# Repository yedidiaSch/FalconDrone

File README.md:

# FalconDrone - RTOS Based Flight Controller

## Project Overview
FalconDrone is an ongoing development of a quadcopter flight control system built from scratch using the **STM32F446RE (Nucleo)** platform. The project focuses on implementing high-performance real-time estimation and control algorithms within a **FreeRTOS** environment.

The current milestone focuses on a "Studio-Tethered" stabilization mode, ensuring the drone maintains its attitude (Roll/Pitch) while secured to a test bench.

## System Architecture
The firmware is designed with a modular, object-oriented approach in C++, emphasizing non-blocking operations and efficient resource management.

### Key Features
* **Real-Time Kernel:** Task management and scheduling via FreeRTOS.
* **Asynchronous I/O:** MPU6050 IMU data acquisition using **I2C DMA** to minimize CPU overhead.
* **Thread-Safe Logging:** Custom UART logging mechanism utilizing **DMA** and FreeRTOS Queues for non-blocking telemetry.
* **Attitude Estimation:** Implementation of raw sensor data processing (Accelerometer and Gyroscope) for Roll/Pitch calculation.

## Hardware Stack
* **MCU:** STM32F446RE (ARM Cortex-M4 @ 180MHz)
* **IMU:** MPU6050 (3-Axis Accelerometer & Gyroscope)
* **Frame:** F450 Quadcopter Frame
* **Motors:** A2212 1000KV Brushless Motors
* **ESCs:** 30A Brushless XXD
* **Power:** 3S Lipo 2200mAh 11.1V

## Software Stack
* **Language:** C++ / C
* **OS:** FreeRTOS
* **Framework:** STM32Cube HAL
* **Build System:** CMake
* **Development Env:** VS Code on Ubuntu

## Current Status: Attitude Estimation Phase
The system currently performs the following:
1.  Initializes hardware peripherals (I2C, UART, DMA, GPIO).
2.  Starts the FreeRTOS scheduler.
3.  Continuously streams 14-byte IMU data packets via DMA.
4.  Processes raw data into Euler angles (Roll and Pitch).

### Forthcoming Milestones
* **Sensor Fusion:** Implementation of a Complementary Filter or Kalman Filter to reduce accelerometer noise and gyroscope drift.
* **PID Control:** Development of the attitude control loop for motor speed regulation.
* **PWM Generation:** Utilizing Timer peripherals to drive ESCs.

## Setup and Installation

### Prerequisites
* GNU Arm Embedded Toolchain
* CMake (minimum 3.10)
* STM32CubeMX (for peripheral configuration)
* OpenOCD / ST-Link Utilities

### Building
```bash
mkdir build
cd build
cmake ..
make

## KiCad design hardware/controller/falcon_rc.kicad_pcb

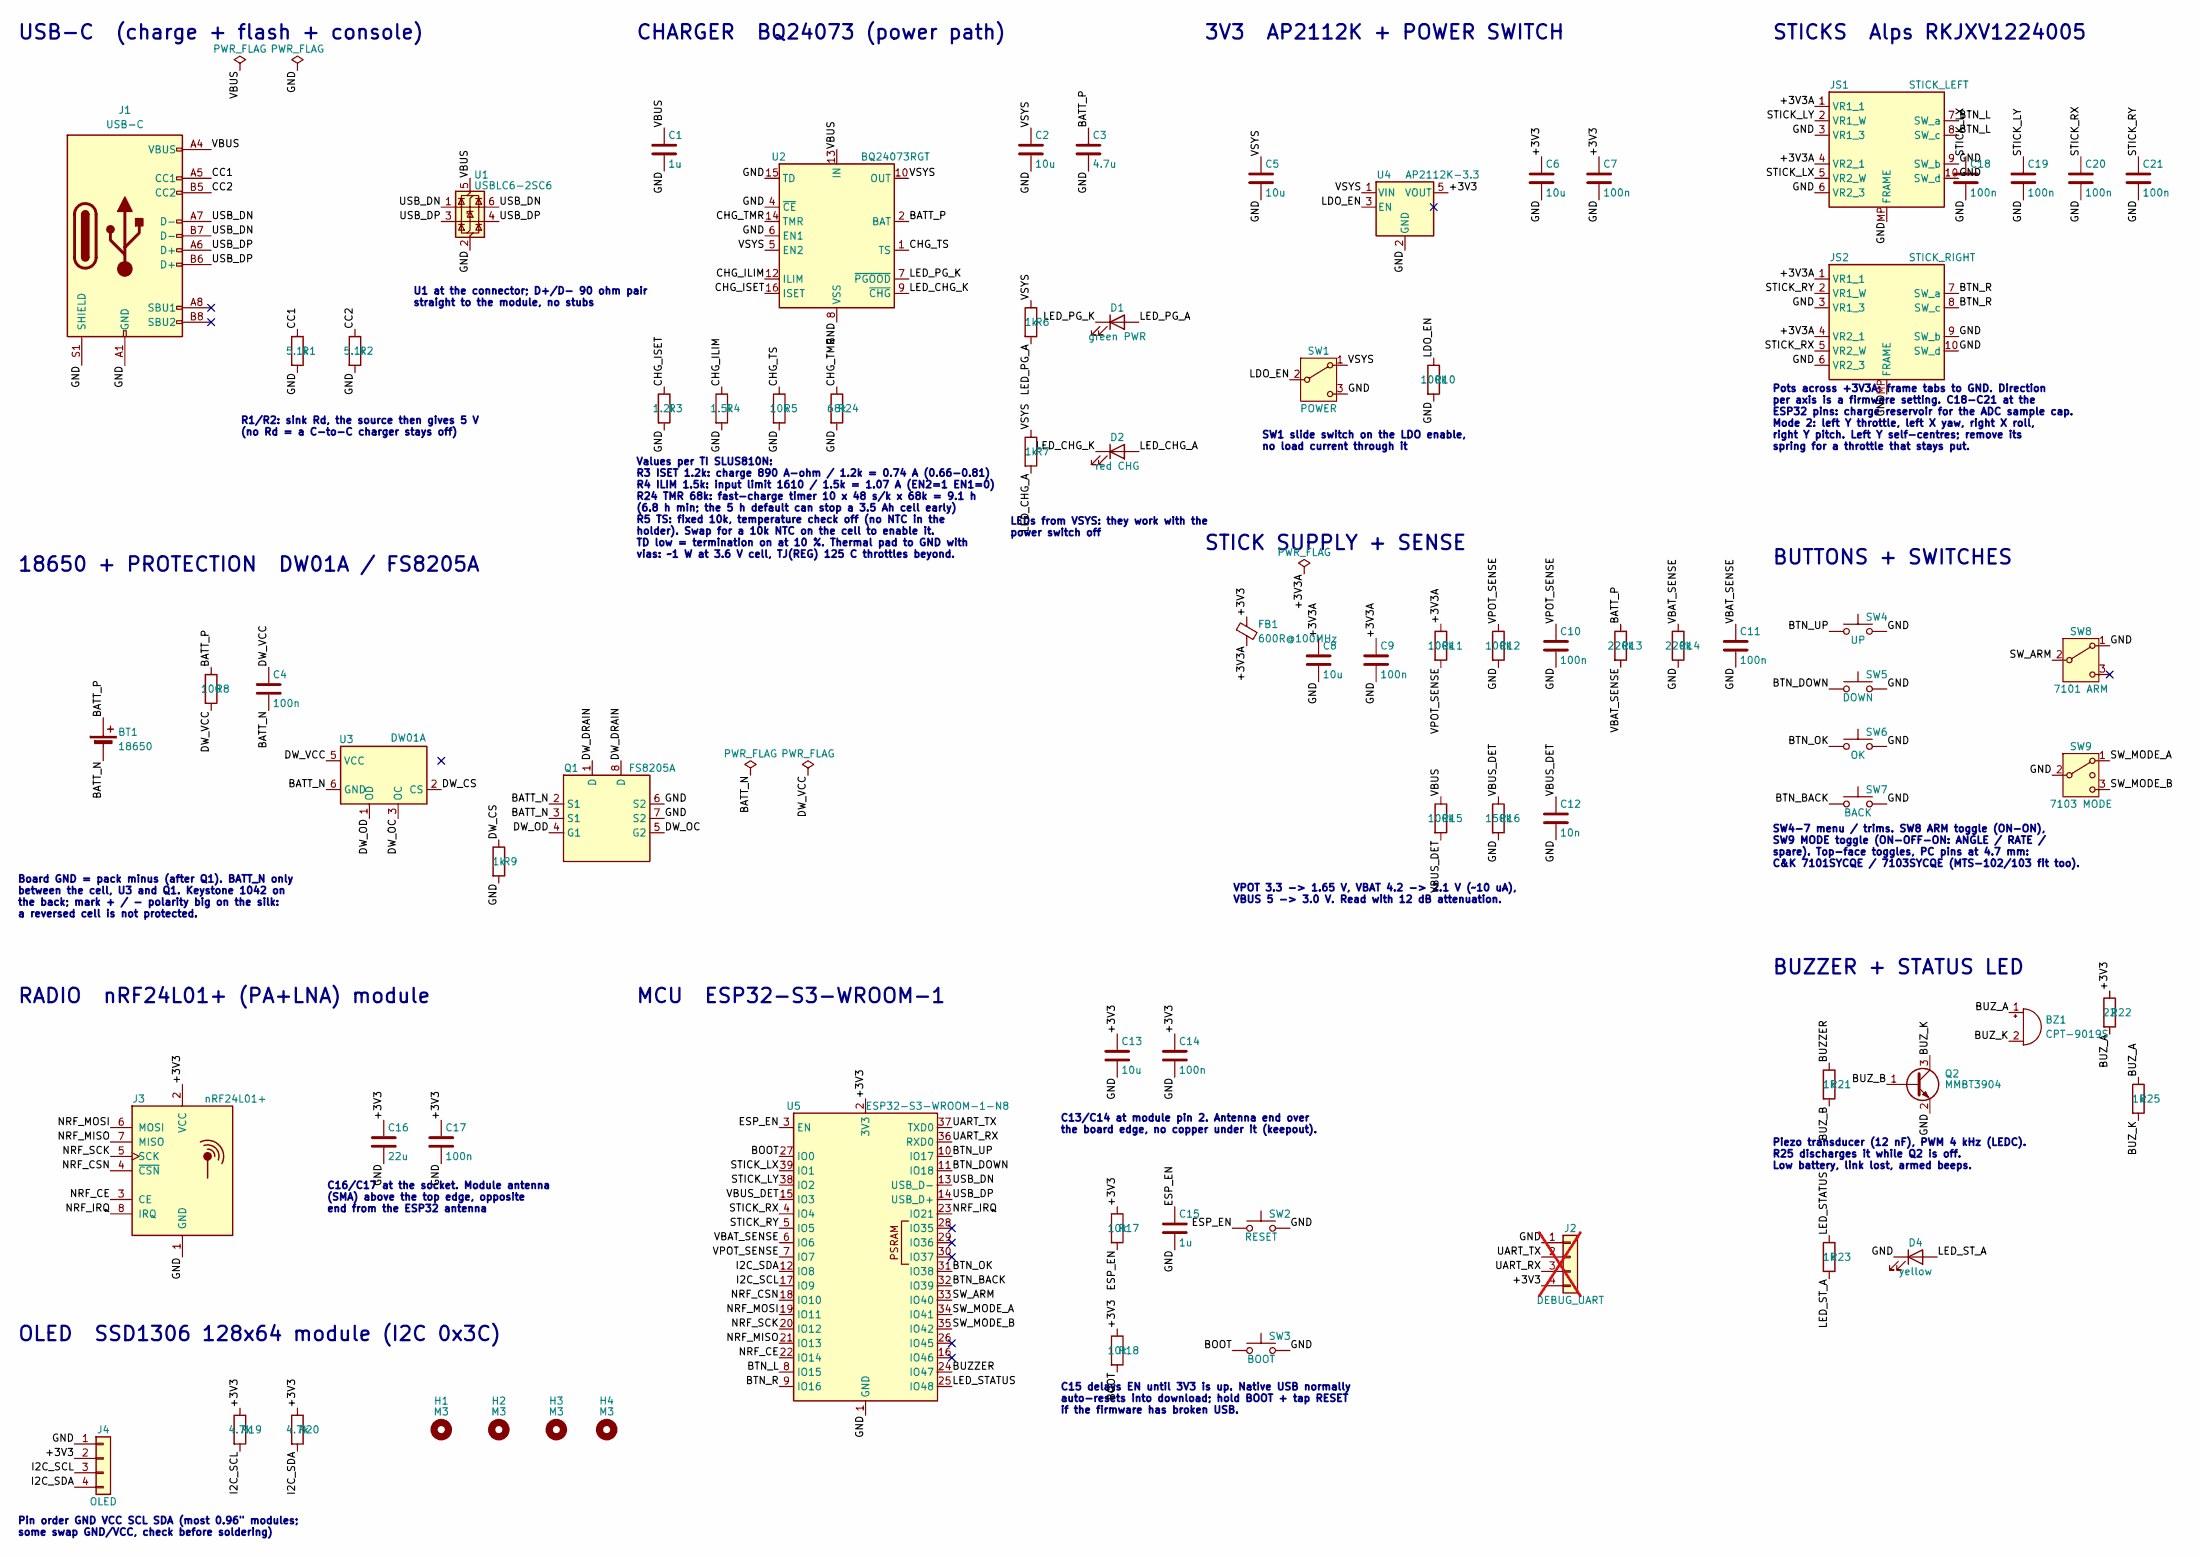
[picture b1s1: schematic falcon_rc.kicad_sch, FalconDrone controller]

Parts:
BT1: 18650; BatteryHolder_Keystone_1042_1x18650
BZ1: CPT-9019S; Buzzer_CUI_CPT-9019S-SMT
C1, C15: 1u; C_0603_1608Metric
C2, C5, C6, C8, C13: 10u; C_0805_2012Metric
C3: 4.7u; C_0805_2012Metric
C4, C7, C9, C10, C11, C14, C17, C18, C19, C20, C21: 100n; C_0603_1608Metric
C12: 10n; C_0603_1608Metric
C16: 22u; C_0805_2012Metric
D1: green PWR; LED_D3.0mm
D2: red CHG; LED_D3.0mm
D4: yellow; LED_D3.0mm
FB1: 600R@100MHz; L_0603_1608Metric
H1, H2, H3, H4: M3; MountingHole_3.2mm_M3
J1: USB-C; USB_C_Receptacle_HRO_TYPE-C-31-M-12
J2: DEBUG_UART; PinHeader_1x04_P2.54mm_Vertical; not fitted
J3: nRF24L01+; nRF24L01_Breakout
J4: OLED; PinSocket_1x04_P2.54mm_Vertical
JS1: STICK_LEFT; Joystick_Alps_RKJXV122400x
JS2: STICK_RIGHT; Joystick_Alps_RKJXV122400x
Q1: FS8205A; TSSOP-8_4.4x3mm_P0.65mm
Q2: MMBT3904; SOT-23
R1, R2: 5.1k; R_0603_1608Metric
R3: 1.2k; R_0603_1608Metric
R4: 1.5k; R_0603_1608Metric
R5, R17, R18: 10k; R_0603_1608Metric
R6, R7, R9, R21, R23, R25: 1k; R_0603_1608Metric
R8: 100; R_0603_1608Metric
R10, R11, R12, R15: 100k; R_0603_1608Metric
R13, R14: 220k; R_0603_1608Metric
R16: 150k; R_0603_1608Metric
R19, R20: 4.7k; R_0603_1608Metric
R22: 22; R_0603_1608Metric
R24: 68k; R_0603_1608Metric
SW1: POWER; SW_SPDT_PCM12
SW2: RESET; SW_SPST_PTS810
SW3: BOOT; SW_SPST_PTS810
SW4: UP; SW_PUSH_6mm_H5mm
SW5: DOWN; SW_PUSH_6mm_H5mm
SW6: OK; SW_PUSH_6mm_H5mm
SW7: BACK; SW_PUSH_6mm_H5mm
SW8: 7101 ARM; Toggle_SPDT_P4.70mm
SW9: 7103 MODE; Toggle_SPDT_P4.70mm
U1: USBLC6-2SC6; SOT-23-6
U2: BQ24073RGT; VQFN-16-1EP_3x3mm_P0.5mm_EP1.6x1.6mm
U3: DW01A; SOT-23-6
U4: AP2112K-3.3; SOT-23-5
U5: ESP32-S3-WROOM-1-N8; ESP32-S3-WROOM-1

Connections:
/+3V3: C6.1, C7.1, C13.1, C14.1, C16.1, C17.1, FB1.1, J2.4, J3.2 (VCC), J4.2, R17.1, R18.1, R19.1, R20.1, R22.1, U4.5 (VOUT), U5.2 (3V3)
/+3V3A: C8.1, C9.1, FB1.2, JS1.1 (VR1_1), JS1.4 (VR2_1), JS2.1 (VR1_1), JS2.4 (VR2_1), R11.1
/BATT_N: BT1.2 (-), C4.2, Q1.2 (S1), Q1.3 (S1), U3.6 (GND)
/BATT_P: BT1.1 (+), C3.1, R8.1, R13.1, U2.2 (BAT), U2.3 (BAT)
/BOOT: R18.2, SW3.1, U5.27 (IO0)
/BTN_BACK: SW7.1, U5.32 (IO39)
/BTN_DOWN: SW5.1, U5.11 (IO18)
/BTN_L: JS1.7 (SW_a), JS1.8 (SW_c), U5.8 (IO15)
/BTN_OK: SW6.1, U5.31 (IO38)
/BTN_R: JS2.7 (SW_a), JS2.8 (SW_c), U5.9 (IO16)
/BTN_UP: SW4.1, U5.10 (IO17)
/BUZZER: R21.1, U5.24 (IO47)
/BUZ_A: BZ1.1 (+), R22.2, R25.1
/BUZ_B: Q2.1 (B), R21.2
/BUZ_K: BZ1.2 (-), Q2.3 (C), R25.2
/CC1: J1.A5 (CC1), R1.1
/CC2: J1.B5 (CC2), R2.1
/CHG_ILIM: R4.1, U2.12 (ILIM)
/CHG_ISET: R3.1, U2.16 (ISET)
/CHG_TMR: R24.1, U2.14 (TMR)
/CHG_TS: R5.1, U2.1 (TS)
/DW_CS: R9.1, U3.2 (CS)
/DW_DRAIN: Q1.1 (D), Q1.8 (D)
/DW_OC: Q1.5 (G2), U3.3 (OC)
/DW_OD: Q1.4 (G1), U3.1 (OD)
/DW_VCC: C4.1, R8.2, U3.5 (VCC)
/ESP_EN: C15.1, R17.2, SW2.1, U5.3 (EN)
/GND: C1.2, C2.2, C3.2, C5.2, C6.2, C7.2, C8.2, C9.2, C10.2, C11.2, C12.2, C13.2, C14.2, C15.2, C16.2, C17.2, C18.2, C19.2, C20.2, C21.2, D4.1 (K), J1.A1 (GND), J1.A12 (GND), J1.B1 (GND), J1.B12 (GND), J1.S1 (SHIELD), J2.1, J3.1 (GND), J4.1, JS1.3 (VR1_3), JS1.6 (VR2_3), JS1.9 (SW_b), JS1.10 (SW_d), JS1.MP (FRAME), JS2.3 (VR1_3), JS2.6 (VR2_3), JS2.9 (SW_b), JS2.10 (SW_d), JS2.MP (FRAME), Q1.6 (S2), Q1.7 (S2), Q2.2 (E), R1.2, R2.2, R3.2, R4.2, R5.2, R9.2, R10.2, R12.2, R14.2, R16.2, R24.2, SW1.3 (C), SW2.2, SW3.2, SW4.2, SW5.2, SW6.2, SW7.2, SW8.1 (A), SW9.2 (3), U1.2 (GND), U2.4 (~CE), U2.6 (EN1), U2.8 (VSS), U2.15 (TD), U2.17 (VSS), U4.2 (GND), U5.1 (GND), U5.40 (GND), U5.41 (GND)
/I2C_SCL: J4.3, R19.2, U5.17 (IO9)
/I2C_SDA: J4.4, R20.2, U5.12 (IO8)
/LDO_EN: R10.1, SW1.2 (B), U4.3 (EN)
/LED_CHG_A: D2.2 (A), R7.2
/LED_CHG_K: D2.1 (K), U2.9 (~CHG)
/LED_PG_A: D1.2 (A), R6.2
/LED_PG_K: D1.1 (K), U2.7 (~PGOOD)
/LED_STATUS: R23.1, U5.25 (IO48)
/LED_ST_A: D4.2 (A), R23.2
/NRF_CE: J3.3 (CE), U5.22 (IO14)
/NRF_CSN: J3.4 (~CSN), U5.18 (IO10)
/NRF_IRQ: J3.8 (IRQ), U5.23 (IO21)
/NRF_MISO: J3.7 (MISO), U5.21 (IO13)
/NRF_MOSI: J3.6 (MOSI), U5.19 (IO11)
/NRF_SCK: J3.5 (SCK), U5.20 (IO12)
/STICK_LX: C18.1, JS1.5 (VR2_W), U5.39 (IO1)
/STICK_LY: C19.1, JS1.2 (VR1_W), U5.38 (IO2)
/STICK_RX: C20.1, JS2.5 (VR2_W), U5.4 (IO4)
/STICK_RY: C21.1, JS2.2 (VR1_W), U5.5 (IO5)
/SW_ARM: SW8.2 (B), U5.33 (IO40)
/SW_MODE_A: SW9.1, U5.34 (IO41)
/SW_MODE_B: SW9.3 (4), U5.35 (IO42)
/UART_RX: J2.3, U5.36 (RXD0)
/UART_TX: J2.2, U5.37 (TXD0)
/USB_DN: J1.A7 (D-), J1.B7 (D-), U1.1 (I/O1), U1.6 (I/O1), U5.13 (USB_D-)
/USB_DP: J1.A6 (D+), J1.B6 (D+), U1.3 (I/O2), U1.4 (I/O2), U5.14 (USB_D+)
/VBAT_SENSE: C11.1, R13.2, R14.1, U5.6 (IO6)
/VBUS: C1.1, J1.A4 (VBUS), J1.A9 (VBUS), J1.B4 (VBUS), J1.B9 (VBUS), R15.1, U1.5 (VBUS), U2.13 (IN)
/VBUS_DET: C12.1, R15.2, R16.1, U5.15 (IO3)
/VPOT_SENSE: C10.1, R11.2, R12.1, U5.7 (IO7)
/VSYS: C2.1, C5.1, R6.1, R7.1, SW1.1 (A), U2.5 (EN2), U2.10 (OUT), U2.11 (OUT), U4.1 (VIN)

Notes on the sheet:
USB-C (charge + flash + console)
R1/R2: sink Rd, the source then gives 5 V (no Rd = a C-to-C charger stays off)
U1 at the connector; D+/D- 90 ohm pair straight to the module, no stubs
CHARGER BQ24073 (power path)
Values per TI SLUS810N: R3 ISET 1.2k: charge 890 A-ohm / 1.2k = 0.74 A (0.66-0.81) R4 ILIM 1.5k: input limit 1610 / 1.5k = 1.07 A (EN2=1 EN1=0) R24 TMR 68k: fast-charge timer 10 x 48 s/k x 68k = 9.1 h (6.8 h min; the 5 h default can stop a 3.5 Ah cell early) R5 TS: fixed 10k, temperature check off 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
LEDs from VSYS: they work with the power switch off
18650 + PROTECTION DW01A / FS8205A
Board GND = pack minus (after Q1). BATT_N only between the cell, U3 and Q1. Keystone 1042 on the back; mark + / - polarity big on the silk: a reversed cell is not protected.
3V3 AP2112K + POWER SWITCH
SW1 slide switch on the LDO enable, no load current through it
STICK SUPPLY + SENSE
VPOT 3.3 -> 1.65 V, VBAT 4.2 -> 2.1 V (~10 uA), VBUS 5 -> 3.0 V. Read with 12 dB attenuation.
MCU ESP32-S3-WROOM-1
C13/C14 at module pin 2. Antenna end over the board edge, no copper under it (keepout).
C15 delays EN until 3V3 is up. Native USB normally auto-resets into download; hold BOOT + tap RESET if the firmware has broken USB.
RADIO nRF24L01+ (PA+LNA) module
C16/C17 at the socket. Module antenna (SMA) above the top edge, opposite end from the ESP32 antenna
OLED SSD1306 128x64 module (I2C 0x3C)
Pin order GND VCC SCL SDA (most 0.96" modules; some swap GND/VCC, check before soldering)
STICKS Alps RKJXV1224005
Pots across +3V3A; frame tabs to GND. Direction per axis is a firmware setting. C18-C21 at the ESP32 pins: charge reservoir for the ADC sample cap. Mode 2: left Y throttle, left X yaw, right X roll, right Y pitch. Left Y self-centres; remove its spring for a throttle that stays put.
BUTTONS + SWITCHES
SW4-7 menu / trims. SW8 ARM toggle (ON-ON), SW9 MODE toggle (ON-OFF-ON: ANGLE / RATE / spare). Top-face toggles, PC pins at 4.7 mm: C&K 7101SYCQE / 7103SYCQE (MTS-102/103 fit too).
BUZZER + STATUS LED
Piezo transducer (12 nF), PWM 4 kHz (LEDC). R25 discharges it while Q2 is off. Low battery, link lost, armed beeps.

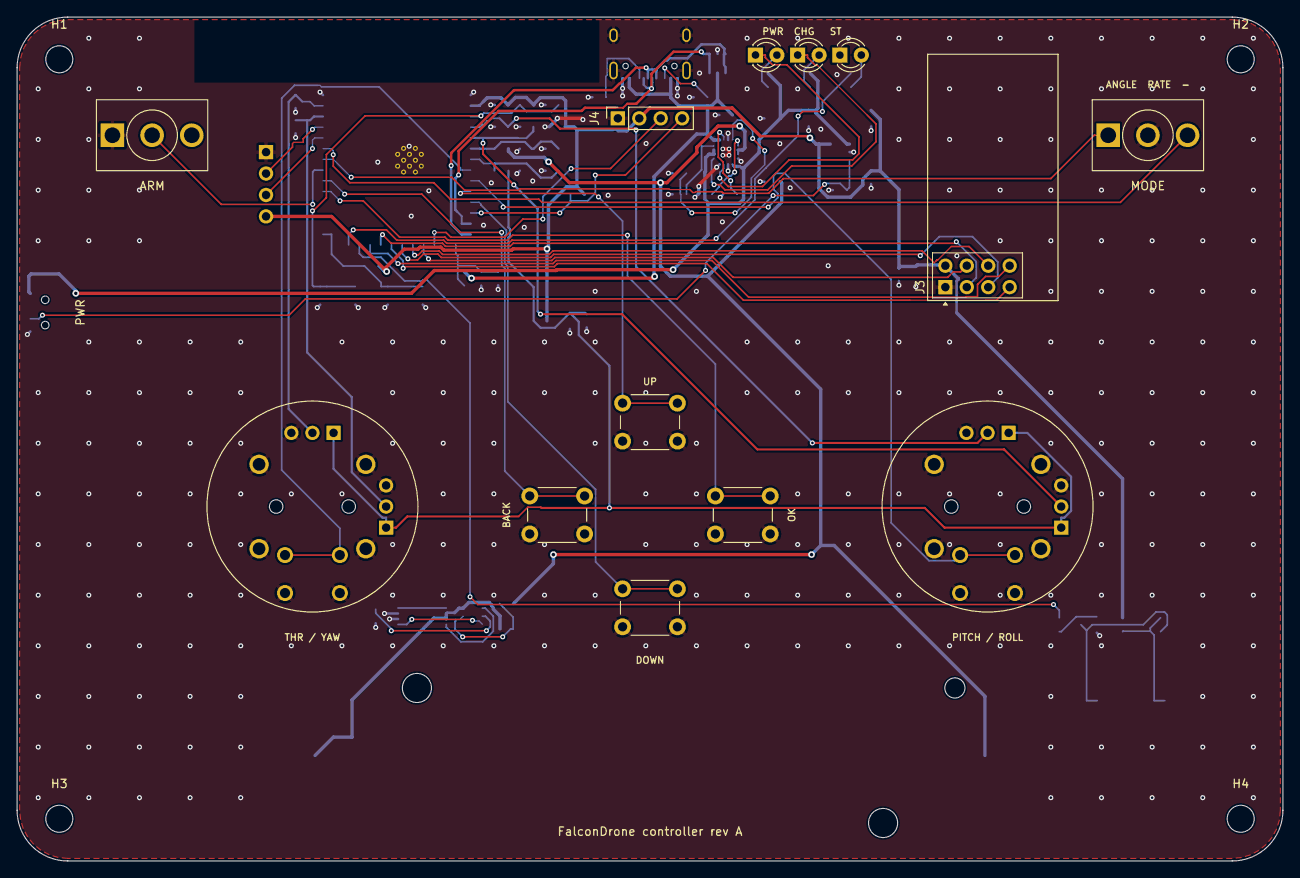
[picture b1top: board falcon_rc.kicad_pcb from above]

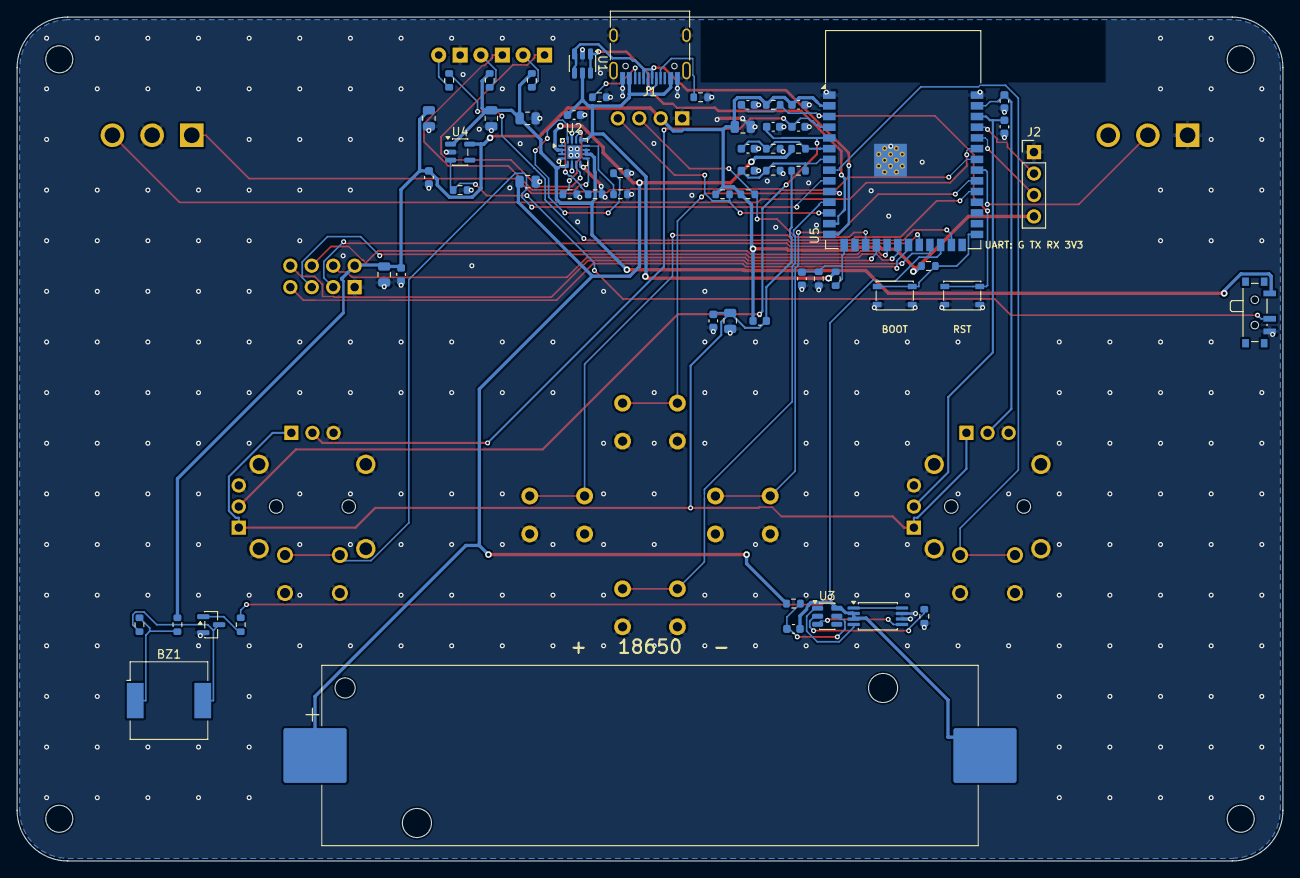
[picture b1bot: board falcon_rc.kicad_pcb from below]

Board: 2 copper layers, 150.0 x 100.0 mm, 78 parts (61 on the bottom side), 59 nets.

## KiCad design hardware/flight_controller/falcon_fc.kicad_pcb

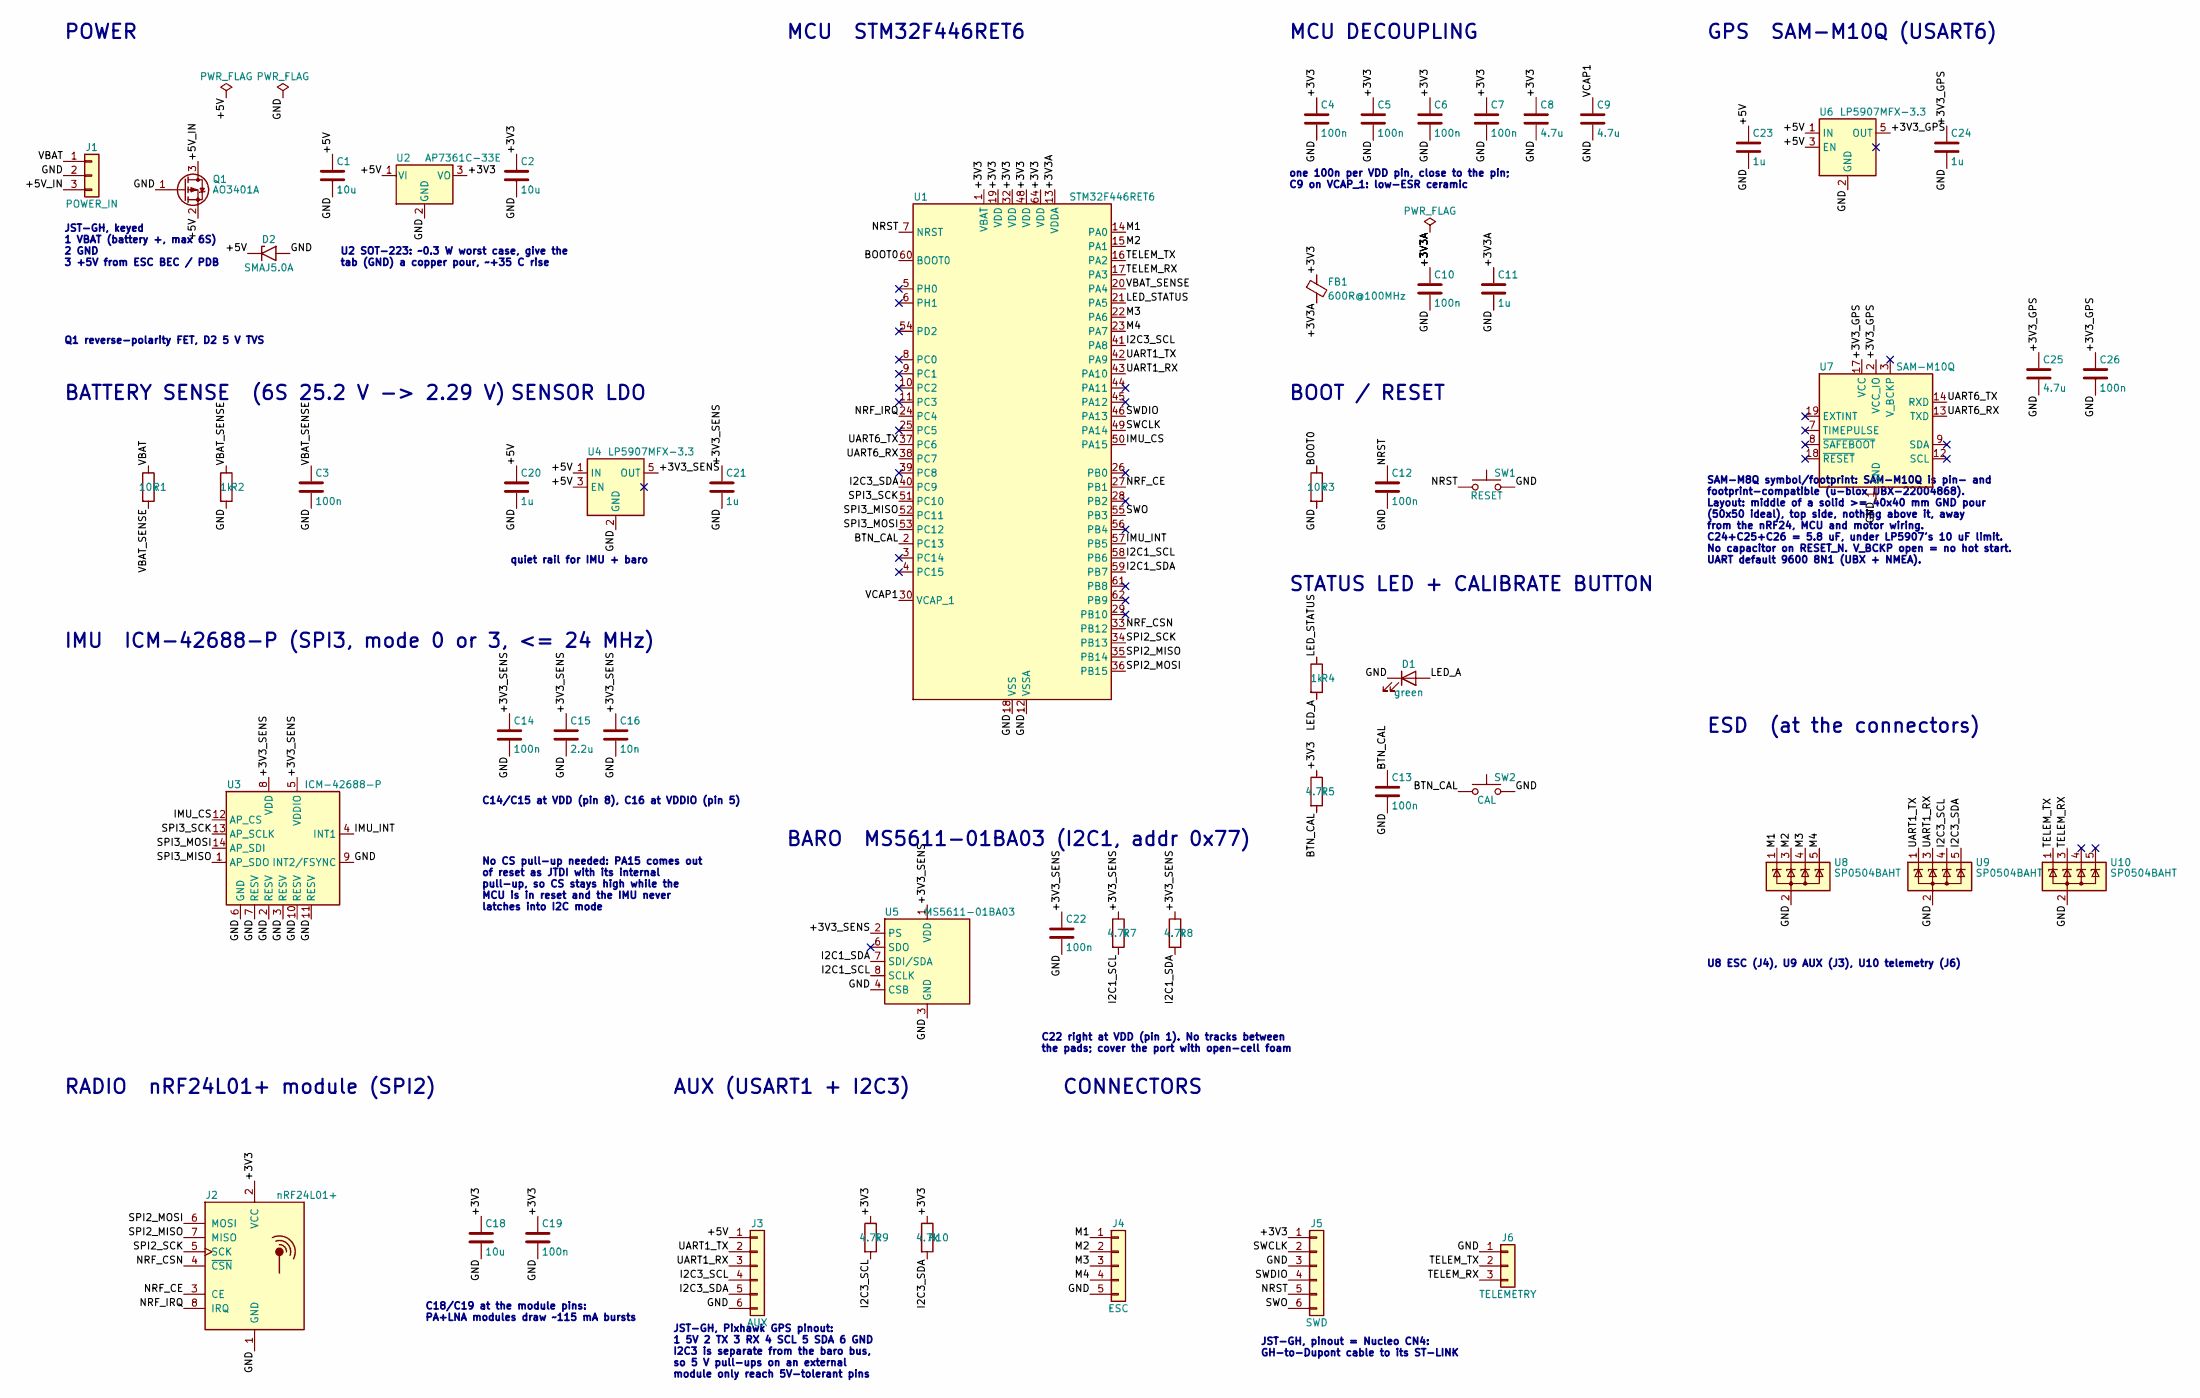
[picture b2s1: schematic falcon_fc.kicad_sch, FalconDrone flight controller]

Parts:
C1, C2, C18: 10u; C_0805_2012Metric
C3, C4, C5, C6, C7, C10, C12, C13, C14, C19, C22, C26: 100n; C_0603_1608Metric
C8, C9, C25: 4.7u; C_0805_2012Metric
C11, C20, C21, C23, C24: 1u; C_0603_1608Metric
C15: 2.2u; C_0603_1608Metric
C16: 10n; C_0603_1608Metric
D1: green; LED_0603_1608Metric
D2: SMAJ5.0A; D_SMA
FB1: 600R@100MHz; L_0603_1608Metric
J1: POWER_IN; JST_GH_SM03B-GHS-TB_1x03-1MP_P1.25mm_Horizontal
J2: nRF24L01+; nRF24L01_Breakout
J3: AUX; JST_GH_SM06B-GHS-TB_1x06-1MP_P1.25mm_Horizontal
J4: ESC; PinHeader_1x05_P2.54mm_Vertical
J5: SWD; JST_GH_SM06B-GHS-TB_1x06-1MP_P1.25mm_Horizontal
J6: TELEMETRY; JST_GH_SM03B-GHS-TB_1x03-1MP_P1.25mm_Horizontal
Q1: AO3401A; SOT-23
R1, R3: 10k; R_0603_1608Metric
R2, R4: 1k; R_0603_1608Metric
R5, R7, R8, R9, R10: 4.7k; R_0603_1608Metric
SW1: RESET; SW_SPST_PTS810
SW2: CAL; SW_SPST_PTS810
U1: STM32F446RET6; LQFP-64_10x10mm_P0.5mm
U2: AP7361C-33E; SOT-223-3_TabPin2
U3: ICM-42688-P; LGA-14_3x2.5mm_P0.5mm_LayoutBorder3x4y
U4, U6: LP5907MFX-3.3; SOT-23-5
U5: MS5611-01BA03; LGA-8_3x5mm_P1.25mm
U7: SAM-M10Q; ublox_SAM-M8Q
U8, U9, U10: SP0504BAHT; SOT-23-5

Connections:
/+3V3: C2.1, C4.1, C5.1, C6.1, C7.1, C8.1, C18.1, C19.1, FB1.1, J2.2 (VCC), J5.1, R5.1, R9.1, R10.1, U1.1 (VBAT), U1.19 (VDD), U1.32 (VDD), U1.48 (VDD), U1.64 (VDD), U2.3 (VO)
/+3V3A: C10.1, C11.1, FB1.2, U1.13 (VDDA)
/+3V3_GPS: C24.1, C25.1, C26.1, U6.5 (OUT), U7.2 (VCC_IO), U7.17 (VCC)
/+3V3_SENS: C14.1, C15.1, C16.1, C21.1, C22.1, R7.1, R8.1, U3.5 (VDDIO), U3.8 (VDD), U4.5 (OUT), U5.1 (VDD), U5.2 (PS)
/+5V: C1.1, C20.1, C23.1, D2.1 (A1), J3.1, Q1.2 (S), U2.1 (VI), U4.1 (IN), U4.3 (EN), U6.1 (IN), U6.3 (EN)
/+5V_IN: J1.3, Q1.3 (D)
/BOOT0: R3.1, U1.60 (BOOT0)
/BTN_CAL: C13.1, R5.2, SW2.1, U1.2 (PC13)
/GND: C1.2, C2.2, C3.2, C4.2, C5.2, C6.2, C7.2, C8.2, C9.2, C10.2, C11.2, C12.2, C13.2, C14.2, C15.2, C16.2, C18.2, C19.2, C20.2, C21.2, C22.2, C23.2, C24.2, C25.2, C26.2, D1.1 (K), D2.2 (A2), J1.2, J2.1 (GND), J3.6, J4.5, J5.3, J6.1, Q1.1 (G), R2.2, R3.2, SW1.2, SW2.2, U1.12 (VSSA), U1.18 (VSS), U1.31 (VSS), U1.47 (VSS), U1.63 (VSS), U2.2 (GND), U3.2 (RESV), U3.3 (RESV), U3.6 (GND), U3.7 (RESV), U3.9 (INT2/FSYNC), U3.10 (RESV), U3.11 (RESV), U4.2 (GND), U5.3 (GND), U5.4 (CSB), U5.5 (CSB), U6.2 (GND), U7.1 (GND), U7.4 (GND), U7.5 (GND), U7.6 (GND), U7.10 (GND), U7.11 (GND), U7.15 (GND), U7.16 (GND), U7.20 (GND), U8.2 (A), U9.2 (A), U10.2 (A)
/I2C1_SCL: R7.2, U1.58 (PB6), U5.8 (SCLK)
/I2C1_SDA: R8.2, U1.59 (PB7), U5.7 (SDI/SDA)
/I2C3_SCL: J3.4, R9.2, U1.41 (PA8), U9.4 (K)
/I2C3_SDA: J3.5, R10.2, U1.40 (PC9), U9.5 (K)
/IMU_CS: U1.50 (PA15), U3.12 (AP_CS)
/IMU_INT: U1.57 (PB5), U3.4 (INT1)
/LED_A: D1.2 (A), R4.2
/LED_STATUS: R4.1, U1.21 (PA5)
/M1: J4.1, U1.14 (PA0), U8.1 (K)
/M2: J4.2, U1.15 (PA1), U8.3 (K)
/M3: J4.3, U1.22 (PA6), U8.4 (K)
/M4: J4.4, U1.23 (PA7), U8.5 (K)
/NRF_CE: J2.3 (CE), U1.27 (PB1)
/NRF_CSN: J2.4 (~CSN), U1.33 (PB12)
/NRF_IRQ: J2.8 (IRQ), U1.24 (PC4)
/NRST: C12.1, J5.5, SW1.1, U1.7 (NRST)
/SPI2_MISO: J2.7 (MISO), U1.35 (PB14)
/SPI2_MOSI: J2.6 (MOSI), U1.36 (PB15)
/SPI2_SCK: J2.5 (SCK), U1.34 (PB13)
/SPI3_MISO: U1.52 (PC11), U3.1 (AP_SDO)
/SPI3_MOSI: U1.53 (PC12), U3.14 (AP_SDI)
/SPI3_SCK: U1.51 (PC10), U3.13 (AP_SCLK)
/SWCLK: J5.2, U1.49 (PA14)
/SWDIO: J5.4, U1.46 (PA13)
/SWO: J5.6, U1.55 (PB3)
/TELEM_RX: J6.3, U1.17 (PA3), U10.3 (K)
/TELEM_TX: J6.2, U1.16 (PA2), U10.1 (K)
/UART1_RX: J3.3, U1.43 (PA10), U9.3 (K)
/UART1_TX: J3.2, U1.42 (PA9), U9.1 (K)
/UART6_RX: U1.38 (PC7), U7.13 (TXD)
/UART6_TX: U1.37 (PC6), U7.14 (RXD)
/VBAT: J1.1, R1.1
/VBAT_SENSE: C3.1, R1.2, R2.1, U1.20 (PA4)
/VCAP1: C9.1, U1.30 (VCAP_1)

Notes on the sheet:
POWER
JST-GH, keyed 1 VBAT (battery +, max 6S) 2 GND 3 +5V from ESC BEC / PDB
Q1 reverse-polarity FET, D2 5 V TVS
U2 SOT-223: ~0.3 W worst case, give the tab (GND) a copper pour, ~+35 C rise
SENSOR LDO
BATTERY SENSE (6S 25.2 V -> 2.29 V)
quiet rail for IMU + baro
MCU STM32F446RET6
MCU DECOUPLING
one 100n per VDD pin, close to the pin; C9 on VCAP_1: low-ESR ceramic
BOOT / RESET
STATUS LED + CALIBRATE BUTTON
IMU ICM-42688-P (SPI3, mode 0 or 3, <= 24 MHz)
C14/C15 at VDD (pin 8), C16 at VDDIO (pin 5)
No CS pull-up needed: PA15 comes out of reset as JTDI with its internal pull-up, so CS stays high while the MCU is in reset and the IMU never latches into I2C mode
BARO MS5611-01BA03 (I2C1, addr 0x77)
C22 right at VDD (pin 1). No tracks between the pads; cover the port with open-cell foam
GPS SAM-M10Q (USART6)
SAM-M8Q symbol/footprint: SAM-M10Q is pin- and footprint-compatible (u-blox UBX-22004868). Layout: middle of a solid >= 40x40 mm GND pour (50x50 ideal), top side, nothing above it, away from the nRF24, MCU and motor wiring. C24+C25+C26 = 5.8 uF, under LP5907's 10 uF limit. No capacitor on RESET_N. 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
ESD (at the connectors)
U8 ESC (J4), U9 AUX (J3), U10 telemetry (J6)
RADIO nRF24L01+ module (SPI2)
C18/C19 at the module pins: PA+LNA modules draw ~115 mA bursts
AUX (USART1 + I2C3)
JST-GH, Pixhawk GPS pinout: 1 5V 2 TX 3 RX 4 SCL 5 SDA 6 GND I2C3 is separate from the baro bus, so 5 V pull-ups on an external module only reach 5V-tolerant pins
CONNECTORS
JST-GH, pinout = Nucleo CN4: GH-to-Dupont cable to its ST-LINK

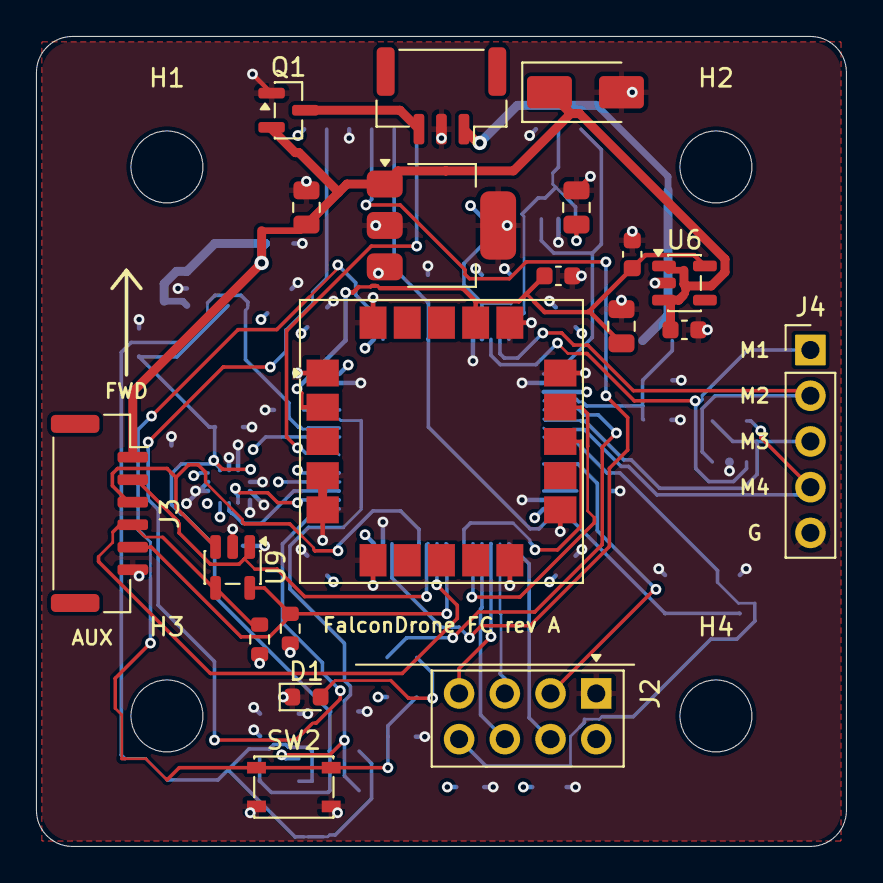
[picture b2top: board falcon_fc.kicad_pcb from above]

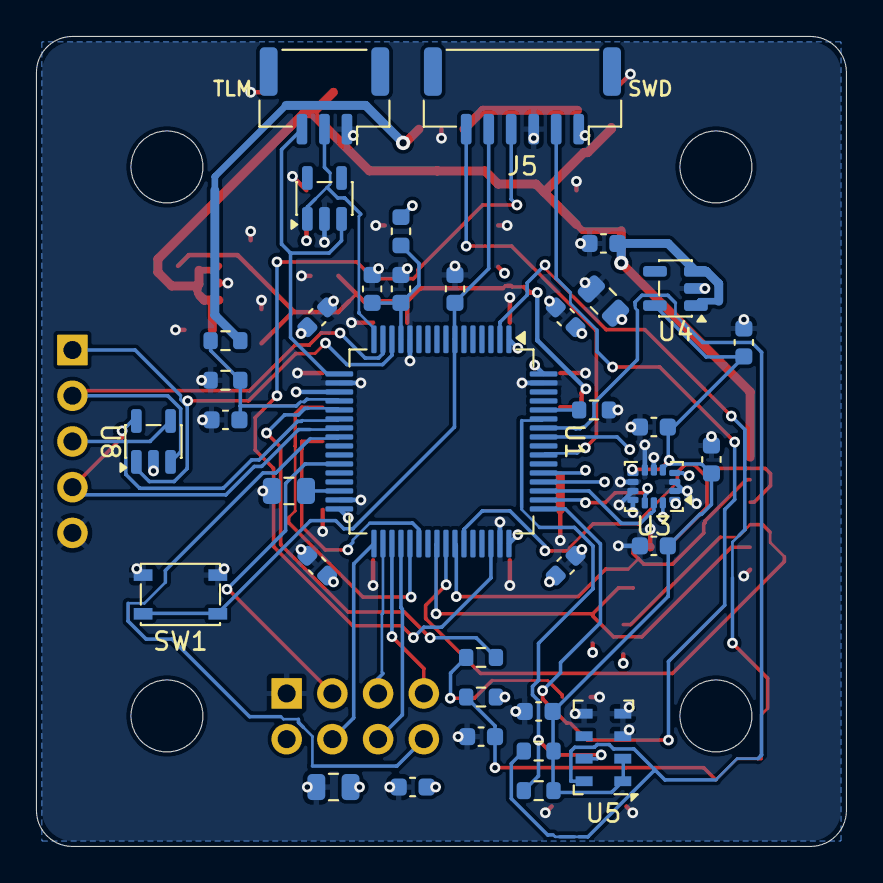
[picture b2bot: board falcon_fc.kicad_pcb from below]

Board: 4 copper layers, 45.0 x 45.0 mm, 60 parts (36 on the bottom side), 43 nets.

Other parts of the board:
H1, H2, H3, H4: MountingHole_4mm

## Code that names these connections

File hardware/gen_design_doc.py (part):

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          controller_diagram(), caption("Figure 2 – controller blocks"),
          p("2.1  Power path", H2),
          p("USB-C feeds a TI <b>BQ24073</b> linear charger with power-path management: its "
            "OUT pin (VSYS) is regulated to 4.4 V while USB is present and switches to the "
            "battery otherwise, so the controller runs while charging and charges while "
            "switched off. The cell is protected in its negative lead by a <b>DW01A</b> with "
            "a dual N-MOSFET <b>8205A</b>; board GND is pack minus. An <b>AP2112K-3.3</b> LDO "
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          table([["Block", "Part", "Notes"],
                 ["MCU", "STM32F446RET6 (LQFP-64)", "one 100 nF per VDD pin, low-ESR ceramic on VCAP_1, "
                  "SWD + SWO on a JST-GH that matches Nucleo CN4"],
                 ["IMU", "TDK ICM-42688-P", "SPI3 ≤ 24 MHz, INT1 to PB5, near the centre of mass"],
                 ["Barometer", "MS5611-01BA03", "I2C1 at 0x77, away from the regulators, cover the "
                  "port with open-cell foam"],
                 ["GPS", "u-blox SAM-M10Q", "USART6, own LP5907 LDO, solid GND under the patch antenna"],
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                 ["Power in", "JST-GH: VBAT, GND, +5 V", "AO3401A reverse-polarity P-FET, SMAJ5.0A TVS"],
                 ["3.3 V", "AP7361C-33E (SOT-223)", "main rail, ≈ 0.3 W worst case into a GND pour"],
                 ["Sensor 3.3 V", "LP5907MFX-3.3", "quiet rail for IMU + baro (+3V3_SENS)"],
                 ["Battery sense", "10k / 1k divider", "6S 25.2 V → 2.29 V on PA4"],
                 ["ESD", "3 × SP0504BAHT", "at the ESC, AUX and telemetry connectors"]],
                [24, 46, 100]),
          p("3.1  Pin map", H2),
          table([["Function", "Pins", "Function", "Pins"],
                 ["ESC M1–M4", "PA0 PA1 (TIM2) · PA6 PA7 (TIM3)", "IMU SPI3", "PC10 SCK · PC11 MISO · PC12 MOSI"],
                 ["nRF24 SPI2", "PB13 SCK · PB14 MISO · PB15 MOSI", "IMU CS / INT1", "PA15 / PB5"],
                 ["nRF24 CSN / CE / IRQ", "PB12 / PB1 / PC4", "Baro I2C1", "PB6 SCL · PB7 SDA"],
                 ["Telemetry USART2", "PA2 TX · PA3 RX", "GPS USART6", "PC6 TX · PC7 RX"],
                 ["AUX USART1 + I2C3", "PA9 PA10 · PA8 PC9", "VBAT_SENSE", "PA4 (ADC)"],
                 ["SWD", "PA13 · PA14 · PB3 SWO", "LED / CAL button", "PA5 / PC13"]],
                [32, 53, 30, 55], mono_cols=(1, 3)),
          p("New pins, not yet in the .ioc: SPI3 IMU, I2C1 baro, PA4 VBAT_SENSE and PC4 NRF_IRQ. "
            "The RC link on this board is the nRF24 only (build with FALCON_RC_RADIO=NRF24).", SMALL),
          p("3.2  PCB", H2),
          table([["Item", "Value"],
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          p("5  Verification status and open items", H1),
          p("Verified", H3),
          *bullets([
              "Charger, protection, LDO, ESD, buzzer driver and FET pinouts checked against the "
              "datasheets (TI SLUS810N, Fortune/HXY 8205A, CUI CPT-9019S, C&amp;K 7000 series).",
              "Pin-by-pin netlist audit of the controller; ERC clean on both schematics; both "
              "boards DRC clean with schematic parity.",
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              "1.07 A input limit can overload a USB-2 port that only allows 500 mA; phone and "
              "USB-C chargers are fine.",
              "Check the OLED module's pin order (GND/VCC) before plugging it in.",
              "Flight controller: add the new pins (SPI3, I2C1, PA4, PC4) to falconDrone.ioc."]),
          ]

    body = os.path.join(BUILD, "body.pdf")
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
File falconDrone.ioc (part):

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Mcu.Name=STM32F446R(C-E)Tx
Mcu.Package=LQFP64
Mcu.UserName=STM32F446RETx
PA0-WKUP.Signal=S_TIM2_CH1_ETR
PA1.Signal=S_TIM2_CH2
PA13.GPIOParameters=GPIO_Label
PA13.GPIO_Label=TMS
PA13.Mode=Serial_Wire
PA13.Signal=SYS_JTMS-SWDIO
PA14.GPIOParameters=GPIO_Label
PA14.GPIO_Label=TCK
PA14.Mode=Serial_Wire
PA14.Signal=SYS_JTCK-SWCLK
PA2.GPIOParameters=GPIO_Label
PA2.GPIO_Label=USART_TX
PA2.Mode=Asynchronous
PA2.Signal=USART2_TX
PA3.GPIOParameters=GPIO_Label
PA3.GPIO_Label=USART_RX
PA3.Mode=Asynchronous
PA3.Signal=USART2_RX
PA5.GPIOParameters=GPIO_Label
PA5.GPIO_Label=LD2 [Green Led]
PA5.Signal=GPIO_Output
PA6.Signal=S_TIM3_CH1
PA7.Signal=S_TIM3_CH2
PB1.GPIOParameters=GPIO_Label
PB1.GPIO_Label=NRF_CE
PB1.Signal=GPIO_Output
PB12.GPIOParameters=PinState,GPIO_Label
PB12.GPIO_Label=NRF_CSN
PB12.PinState=GPIO_PIN_SET
PB12.Signal=GPIO_Output
PB13.Mode=Full_Duplex_Master
PB13.Signal=SPI2_SCK
PB14.Mode=Full_Duplex_Master
PB14.Signal=SPI2_MISO
PB15.Mode=Full_Duplex_Master
PB15.Signal=SPI2_MOSI
PB3.GPIOParameters=GPIO_Label
PB3.GPIO_Label=SWO
PB3.Signal=SYS_JTDO-SWO
PB6.Mode=I2C
PB6.Signal=I2C1_SCL
PB7.Mode=I2C
PB7.Signal=I2C1_SDA
PC13.GPIOParameters=GPIO_Label,GPIO_ModeDefaultEXTI
PC13.GPIO_Label=B1 [Blue PushButton]
PC13.GPIO_ModeDefaultEXTI=GPIO_MODE_IT_FALLING
PC13.Signal=GPXTI13
PC14-OSC32_IN.Mode=LSE-External-Oscillator
PC14-OSC32_IN.Signal=RCC_OSC32_IN
PC15-OSC32_OUT.Mode=LSE-External-Oscillator
PC15-OSC32_OUT.Signal=RCC_OSC32_OUT
PH0-OSC_IN.Mode=HSE-External-Oscillator
PH0-OSC_IN.Signal=RCC_OSC_IN
PH1-OSC_OUT.Mode=HSE-External-Oscillator
PH1-OSC_OUT.Signal=RCC_OSC_OUT
RCC.HSE_VALUE=8000000
RCC.SYSCLKFreq_VALUE=180000000
RCC.SYSCLKSource=RCC_SYSCLKSOURCE_PLLCLK
board=NUCLEO-F446RE
boardIOC=true

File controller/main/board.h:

#ifndef BOARD_H
#define BOARD_H

/*
 * ESP32-WROOM-32 DevKit pin map. Everything runs at 3.3 V — including the
 * joystick (its "+5V" pin goes to 3V3: more than 3.3 V on a GPIO damages it).
 *
 *   nRF24L01+   only with the nRF24 transport (menuconfig), not needed
 *               for ESP-NOW. VCC→3V3 (+ 10-100 uF cap at the module), GND,
 *               CE→D4, CSN→D5, SCK→D18, MOSI→D23, MISO→D19
 *   OLED        SSD1306 128x64, VCC→3V3, GND, SDA→D21, SCL→D22
 *   Slider      ends→3V3/GND, wiper→D34
 *   Joystick    VRx→D32, VRy→D33, SW→D25
 *   Switches    ARM: middle pin→D26, one end pin→GND (other end free)
 *               MODE: middle pin→D27, one end pin→GND (other end free)
 *
 * Analog inputs must stay on ADC1 (GPIO32-39): ADC2 is unusable while the
 * Wi-Fi driver is active, so it is avoided altogether.
 */

#include "driver/gpio.h"

/* nRF24 — SPI3_HOST (VSPI) */
#define PIN_NRF_SCK     GPIO_NUM_18
#define PIN_NRF_MOSI    GPIO_NUM_23
#define PIN_NRF_MISO    GPIO_NUM_19
#define PIN_NRF_CSN     GPIO_NUM_5
#define PIN_NRF_CE      GPIO_NUM_4

/* SSD1306 OLED — I2C */
#define PIN_OLED_SDA    GPIO_NUM_21
#define PIN_OLED_SCL    GPIO_NUM_22
#define OLED_I2C_ADDR   0x3C

/* Analog inputs (ADC1) */
#define PIN_THROTTLE    GPIO_NUM_34   /* ADC1_CH6 */
#define PIN_STICK_X     GPIO_NUM_32   /* ADC1_CH4 — roll  */
#define PIN_STICK_Y     GPIO_NUM_33   /* ADC1_CH5 — pitch */

/* Joystick push button, active low (internal pull-up) */
#define PIN_STICK_SW    GPIO_NUM_25

/* Slide switches to GND, internal pull-up. Which level means ON is set in
 * inputs.c (depends on which end pin was wired to GND). */
#define PIN_ARM_SW      GPIO_NUM_26
#define PIN_MODE_SW     GPIO_NUM_27

#endif /* BOARD_H */

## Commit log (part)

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2025-06-26 Add STM32 FreeRTOS CMake skeleton
2025-06-30 Added FreeRTOS as submodule and cleaned build artifacts
2026-01-06 restart project - 6.1.2026
2026-01-06 update HW
2026-01-07 update jan 7 - C++
2026-01-11 11.1
2026-01-11 Add i2c read imu6050 with DMA
2026-01-11 add gyro to print
2026-01-11 readme file
2026-01-11 Documentations
2026-01-26 add filter to mpu
2026-01-26 Remove venv from tracking and add to .gitignore
2026-01-27 add logger-dma
